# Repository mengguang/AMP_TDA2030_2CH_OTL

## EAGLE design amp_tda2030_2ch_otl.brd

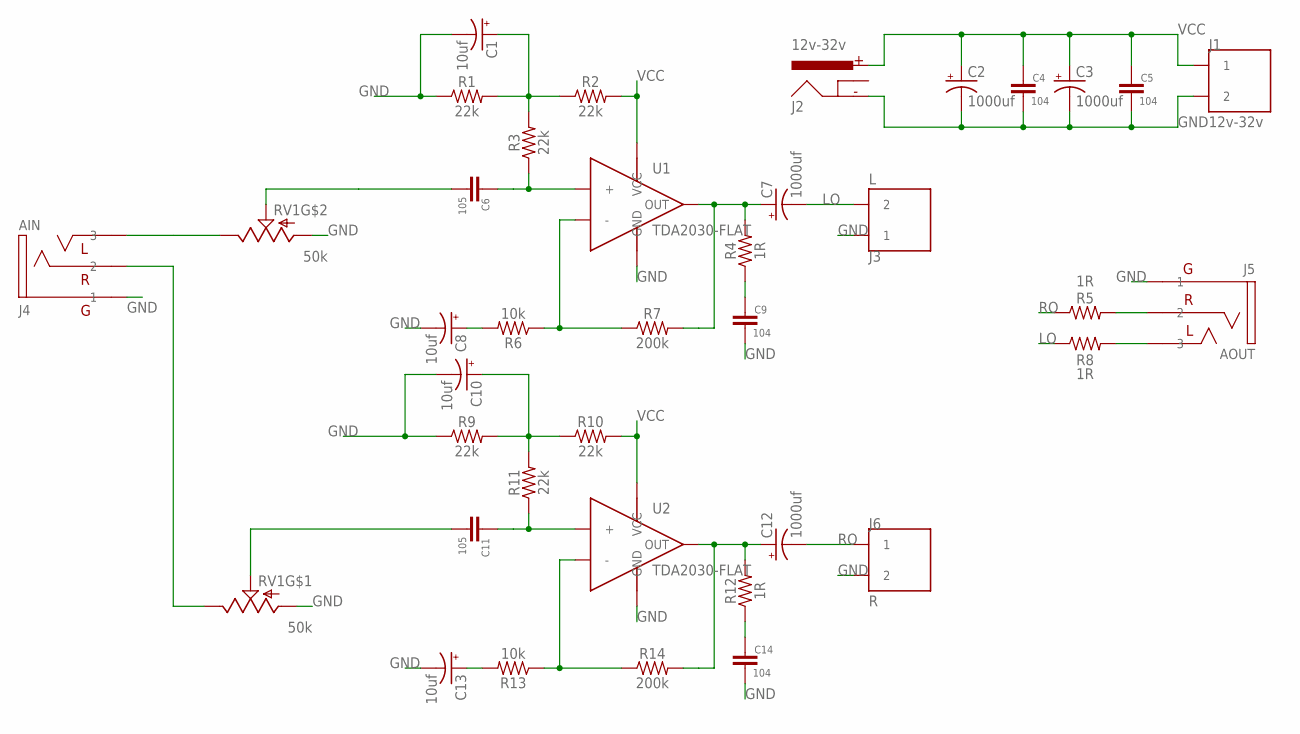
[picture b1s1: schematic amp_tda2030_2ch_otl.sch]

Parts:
C1, C8, C10, C13: 10uf; CAP_2.5MM
C2, C3, C7, C12: 1000uf; CAP_5MM_10D
C4, C5, C9, C14: 104; CAP_5MM
C6, C11: 105; CAP_5MM
J1: 12v-32v; 2P_5.08MM
J2: 12v-32v; POWER_JACK_PTH_LOCK
J3: L; 2P_5.08MM
J4: AIN; 3.5MM
J5: AOUT; 3.5MM
J6: R; 2P_5.08MM
R1, R2, R3, R9, R10, R11: 22k; AXIAL-0.3
R4, R12: 1R; AXIAL-0.3
R5, R8: 1R; 2WS
R6, R13: 10k; AXIAL-0.3
R7, R14: 200k; AXIAL-0.3
RV1: 50k; POT_DUAL_GREEN
U1, U2: TDA2030-FLAT; TO220-FLAT

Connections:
GND: C1.-, C2.-, C3.-, C4.P$2 (2), C5.P$2 (2), C8.-, C9.P$2 (2), C10.-, C13.-, C14.P$2 (2), J1.N (2), J2.GND, J3.L (1), J4.P$1 (1), J5.P$1 (1), J6.N (2), R1.P$1 (1), R9.P$1 (1), RV1.P$1 (A), RV1.P$4 (A), U1.3 (GND), U1.TAB (GND), U2.3 (GND), U2.TAB (GND)
LO: C7.-, J3.N (2), R8.P$1 (1)
unnamed: C6.P$1 (1), R3.P$1 (1), U1.1 (+)
unnamed: C6.P$2 (2), RV1.P$5 (S)
unnamed: C11.P$2 (2), RV1.P$2 (S)
unnamed: C1.+, R1.P$2 (2), R2.P$1 (1), R3.P$2 (2)
unnamed: C8.+, R6.P$2 (2)
unnamed: R6.P$1 (1), R7.P$1 (1), U1.2 (-)
unnamed: J4.P$3 (3), RV1.P$6 (E)
unnamed: J4.P$2 (2), RV1.P$3 (E)
unnamed: C11.P$1 (1), R11.P$1 (1), U2.1 (+)
unnamed: C7.+, R4.P$2 (2), R7.P$2 (2), U1.4 (OUT)
unnamed: J5.P$2 (2), R5.P$2 (2)
unnamed: C9.P$1 (1), R4.P$1 (1)
unnamed: C10.+, R9.P$2 (2), R10.P$1 (1), R11.P$2 (2)
unnamed: C13.+, R13.P$2 (2)
unnamed: R13.P$1 (1), R14.P$1 (1), U2.2 (-)
unnamed: C12.+, R12.P$2 (2), R14.P$2 (2), U2.4 (OUT)
unnamed: C14.P$1 (1), R12.P$1 (1)
unnamed: J5.P$3 (3), R8.P$2 (2)
RO: C12.-, J6.L (1), R5.P$1 (1)
VCC: C2.+, C3.+, C4.P$1 (1), C5.P$1 (1), J1.L (1), J2.PWR, R2.P$2 (2), R10.P$2 (2), U1.5 (VCC), U2.5 (VCC)

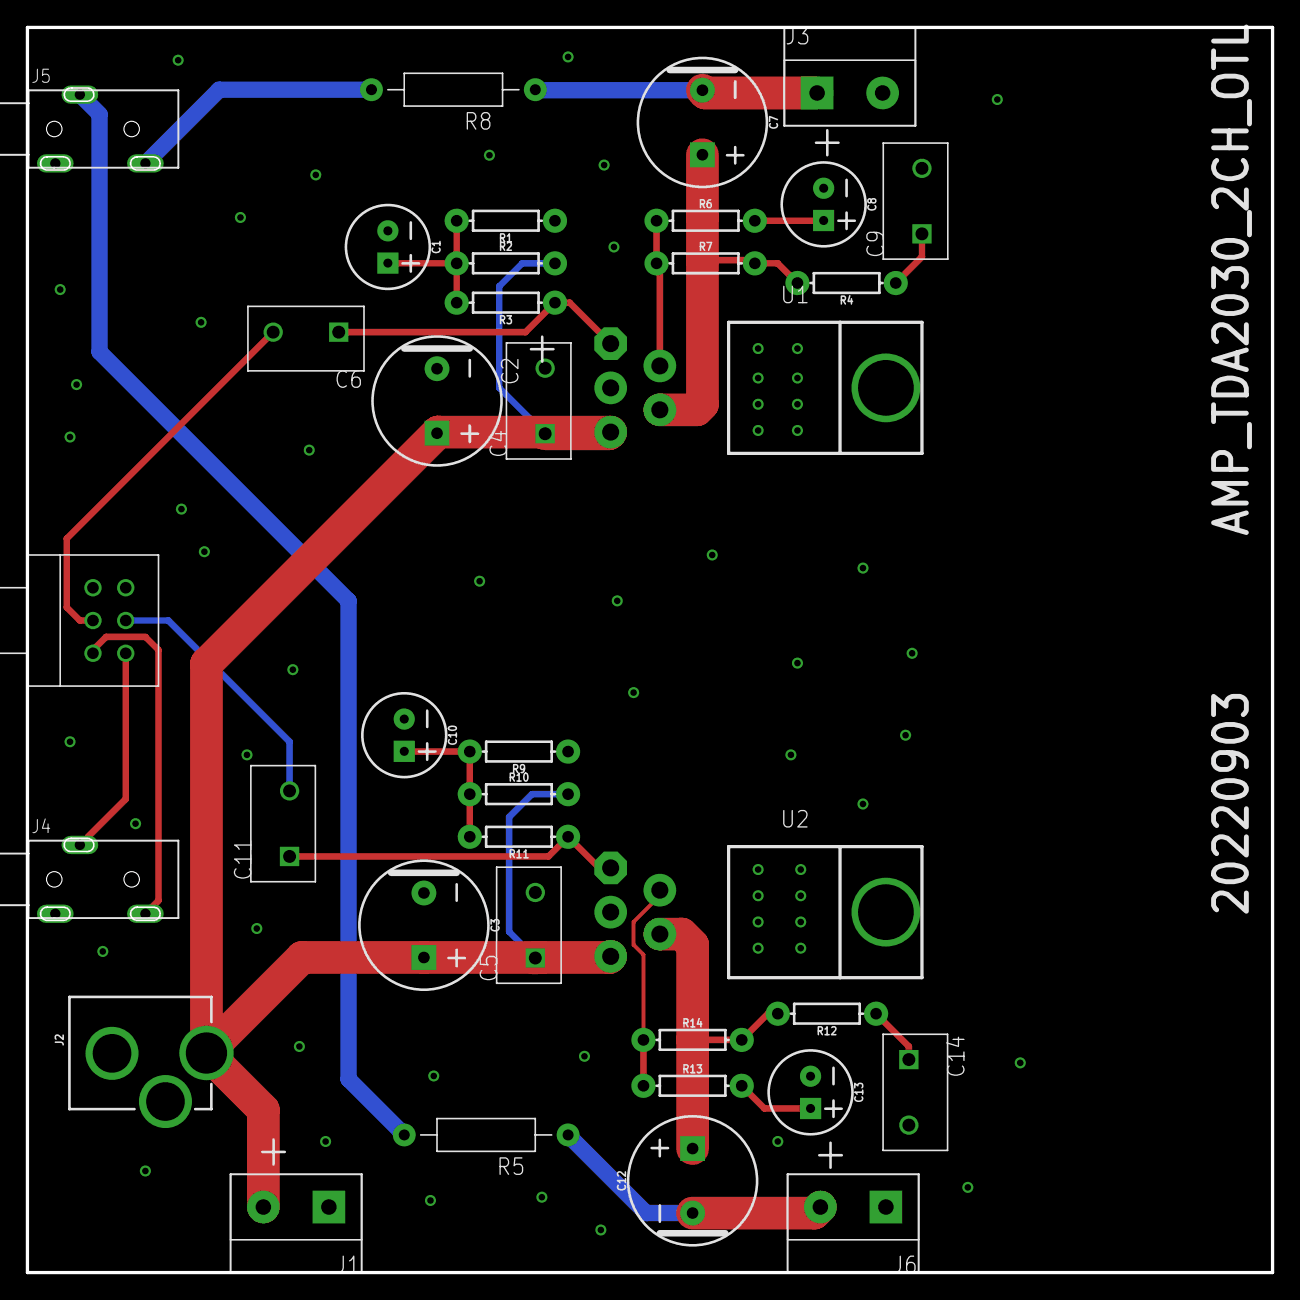
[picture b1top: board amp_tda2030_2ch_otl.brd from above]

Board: 2 copper layers, 96.5 x 96.5 mm, 37 parts (0 on the bottom side), 22 nets.

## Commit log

2022-09-06 20220903
